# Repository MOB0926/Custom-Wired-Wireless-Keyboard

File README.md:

### Custom-Wired-Wireless-Keyboard

## What Is This?

- This is my entry for Hackclub's 'KEEB' YSWS

- I designed a Custom TKL keyboard. I designed a PCB and a 3D-Printed Case to house the PCB

- My keyboard features 80 Keys in the standard orientation and order of a keyboard. In addition to an EC11 Rotary encoder for Volume Adjustment and a 0.91 in OLED to display whatever I want. As the circuit is controlled by a WEMOS LOLIN ESP32 S3 Mini, I have included wireless functionality through its onboard BLE, along with an internal 18650 battery and charging unit to supply power during wireless use.

## Design Preview

## PCB

## Challenges 

- Price. PCBs over 100x100mm are very expensive, along with all the other components this may have been my most dificult project for finding cost effective solutions

- Size. The case is massive and no printer I own or have acces too will allow me to print this so I had to think about that as I designed.

- Procrastination. I had 3 months to do this and for some reason took like 3 week breaks in between entries at the begining

## What I learned

- This is my first time implementing a battery into a project so it was quite the new experience

- I have never designed or even built a Keyboard in my life (Excluding the Blueprint Hack-Pad) so I learnt a lot about how they work and the many different ways the case can come together.

- 3ple check every measurement before basing a design choice on it and then coming back after 4 hours of work just for it to be completetly wrong

## Why 

- Free Keyboard Obviously (Well if instead of putting all this time into this and I got a job instead I think I would have more than a $90 grant)

- Cool thing to show off

- Experience and knowledge for the future that will hopefully help me get a good career 

## CAD

- [OnShape Link](https://cad.onshape.com/documents/53f04297178249ea44cfb3cb/w/90fdca30b2683fca6e7d0462/e/9a4dc5cee2a441016592482a?renderMode=0&uiState=6ae65793278064ead9cd5df0)

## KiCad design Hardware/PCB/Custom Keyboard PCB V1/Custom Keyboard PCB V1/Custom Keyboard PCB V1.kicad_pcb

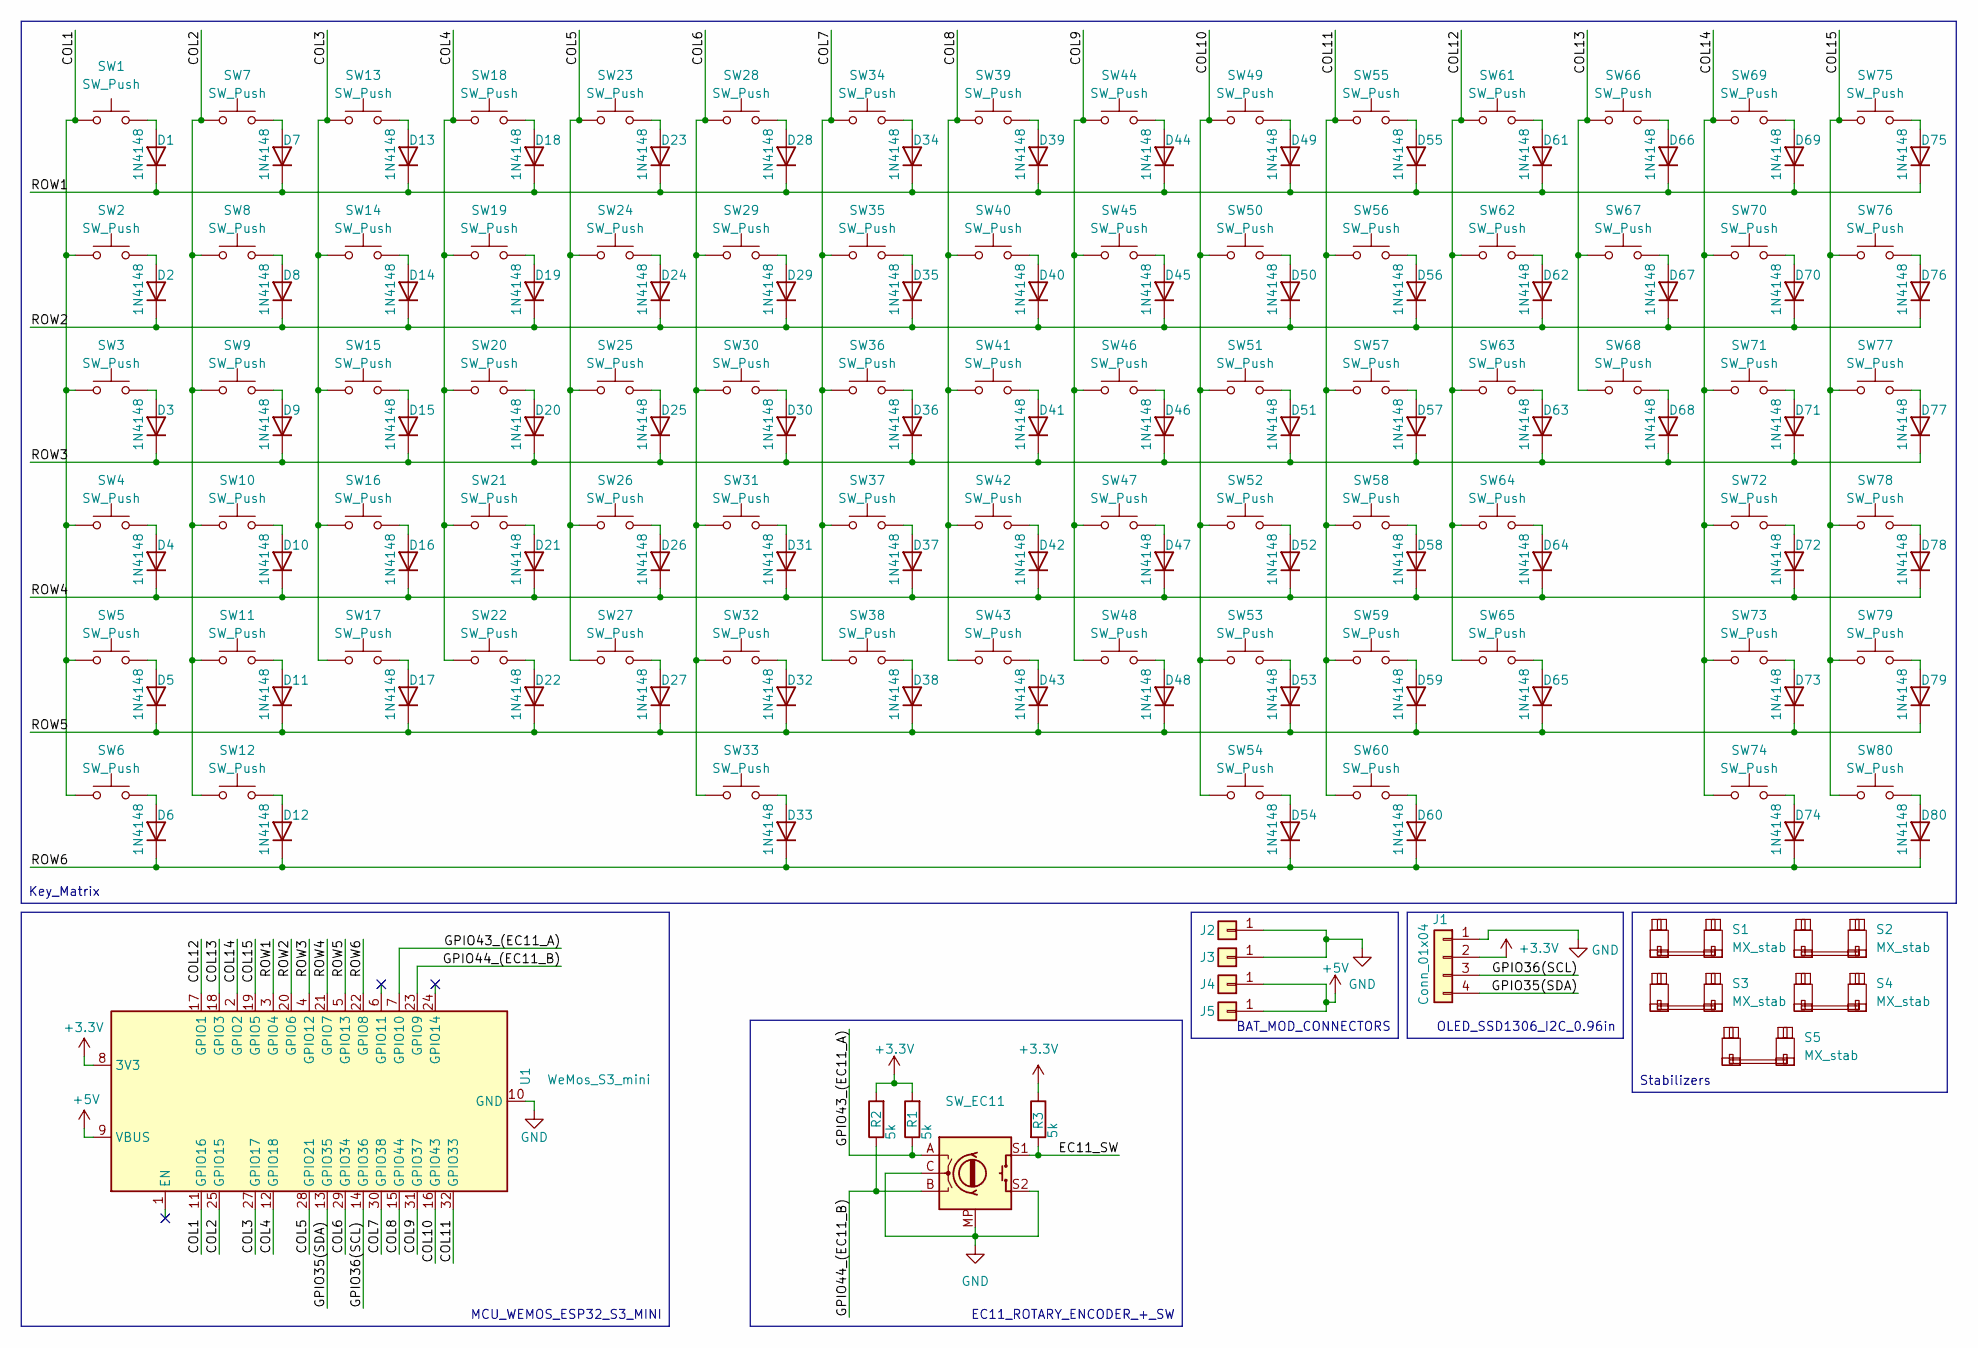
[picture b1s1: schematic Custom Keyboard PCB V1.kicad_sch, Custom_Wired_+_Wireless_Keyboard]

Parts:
D1, D2, D3, D4, D5, D6, D7, D8, D9, D10, D11, D12, D13, D14, D15, D16, D17, D18, D19, D20, D21, D22, D23, D24, D25, D26, D27, D28, D29, D30, D31, D32, D33, D34, D35, D36, D37, D38, D39, D40, D41, D42, D43, D44, D45, D46, D47, D48, D49, D50, D51, D52, D53, D54, D55, D56, D57, D58, D59, D60, D61, D62, D63, D64, D65, D66, D67, D68, D69, D70, D71, D72, D73, D74, D75, D76, D77, D78, D79, D80: 1N4148; D_MiniMELF_Handsoldering
J1: Conn_01x04; OLED_SSD1306_I2C_0.96
J2, J3, J4, J5: Conn_01x01; PinHeader_1x01_P2.54mm_Vertical
R1, R2, R3: 5k; R_Axial_DIN0204_L3.6mm_D1.6mm_P5.08mm_Horizontal
S1, S2, S3, S4: MX_stab; STAB_MX_P_2u
S5: MX_stab; STAB_MX_P_6.25u
SW1, SW2, SW3, SW4, SW5, SW6, SW7, SW8, SW9, SW10, SW11, SW12, SW13, SW14, SW15, SW16, SW17, SW18, SW19, SW20, SW21, SW22, SW23, SW24, SW25, SW26, SW27, SW28, SW29, SW30, SW31, SW32, SW33, SW34, SW35, SW36, SW37, SW38, SW39, SW40, SW41, SW42, SW43, SW44, SW45, SW46, SW47, SW48, SW49, SW50, SW51, SW52, SW53, SW54, SW55, SW56, SW57, SW58, SW59, SW60, SW61, SW62, SW63, SW64, SW65, SW66, SW67, SW68, SW69, SW70, SW71, SW72, SW73, SW74, SW75, SW76, SW77, SW78, SW79, SW80: SW_Push; SW_MX_1u
SW_EC11: RotaryEncoder_Switch_MP; RotaryEncoder_Alps_EC11E-Switch_Vertical_H20mm_MountingHoles
U1: WeMos_S3_mini; WEMOS_S2_mini

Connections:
+3.3V: J1.2, R1.2, R2.2, R3.1, U1.8 (3V3)
+5V: J4.1 (Pin_1_1), J5.1 (Pin_1_1), U1.9 (VBUS)
/COL1: SW1.1, SW2.1, SW3.1, SW4.1, SW5.1, SW6.1, U1.11 (GPIO16)
/COL2: SW7.1, SW8.1, SW9.1, SW10.1, SW11.1, SW12.1, U1.25 (GPIO15)
/COL3: SW13.1, SW14.1, SW15.1, SW16.1, SW17.1, U1.27 (GPIO17)
/COL4: SW18.1, SW19.1, SW20.1, SW21.1, SW22.1, U1.12 (GPIO18)
/COL5: SW23.1, SW24.1, SW25.1, SW26.1, SW27.1, U1.28 (GPIO21)
/COL6: SW28.1, SW29.1, SW30.1, SW31.1, SW32.1, SW33.1, U1.29 (GPIO34)
/COL7: SW34.1, SW35.1, SW36.1, SW37.1, SW38.1, U1.30 (GPIO38)
/COL8: SW39.1, SW40.1, SW41.1, SW42.1, SW43.1, U1.15 (GPIO44)
/COL9: SW44.1, SW45.1, SW46.1, SW47.1, SW48.1, U1.31 (GPIO37)
/COL10: SW49.1, SW50.1, SW51.1, SW52.1, SW53.1, SW54.1, U1.16 (GPIO43)
/COL11: SW55.1, SW56.1, SW57.1, SW58.1, SW59.1, SW60.1, U1.32 (GPIO33)
/COL12: SW61.1, SW62.1, SW63.1, SW64.1, SW65.1, U1.17 (GPIO1)
/COL13: SW66.1, SW67.1, SW68.1, U1.18 (GPIO3)
/COL14: SW69.1, SW70.1, SW71.1, SW72.1, SW73.1, SW74.1, U1.2 (GPIO2)
/COL15: SW75.1, SW76.1, SW77.1, SW78.1, SW79.1, SW80.1, U1.19 (GPIO5)
/EC11_SW: R3.2, SW_EC11.S1
/GPIO35(SDA): J1.4, U1.13 (GPIO35)
/GPIO36(SCL): J1.3, U1.14 (GPIO36)
/GPIO43_(EC11_A): R1.1, SW_EC11.A, U1.7 (GPIO10)
/GPIO44_(EC11_B): R2.1, SW_EC11.B, U1.23 (GPIO9)
/ROW1: D1.1 (K), D7.1 (K), D13.1 (K), D18.1 (K), D23.1 (K), D28.1 (K), D34.1 (K), D39.1 (K), D44.1 (K), D49.1 (K), D55.1 (K), D61.1 (K), D66.1 (K), D69.1 (K), D75.1 (K), U1.3 (GPIO4)
/ROW2: D2.1 (K), D8.1 (K), D14.1 (K), D19.1 (K), D24.1 (K), D29.1 (K), D35.1 (K), D40.1 (K), D45.1 (K), D50.1 (K), D56.1 (K), D62.1 (K), D67.1 (K), D70.1 (K), D76.1 (K), U1.20 (GPIO6)
/ROW3: D3.1 (K), D9.1 (K), D15.1 (K), D20.1 (K), D25.1 (K), D30.1 (K), D36.1 (K), D41.1 (K), D46.1 (K), D51.1 (K), D57.1 (K), D63.1 (K), D68.1 (K), D71.1 (K), D77.1 (K), U1.4 (GPIO12)
/ROW4: D4.1 (K), D10.1 (K), D16.1 (K), D21.1 (K), D26.1 (K), D31.1 (K), D37.1 (K), D42.1 (K), D47.1 (K), D52.1 (K), D58.1 (K), D64.1 (K), D72.1 (K), D78.1 (K), U1.21 (GPIO7)
/ROW5: D5.1 (K), D11.1 (K), D17.1 (K), D22.1 (K), D27.1 (K), D32.1 (K), D38.1 (K), D43.1 (K), D48.1 (K), D53.1 (K), D59.1 (K), D65.1 (K), D73.1 (K), D79.1 (K), U1.5 (GPIO13)
/ROW6: D6.1 (K), D12.1 (K), D33.1 (K), D54.1 (K), D60.1 (K), D74.1 (K), D80.1 (K), U1.22 (GPIO8)
GND: J1.1, J2.1 (Pin_1_1), J3.1 (Pin_1_1), SW_EC11.C, SW_EC11.MP, SW_EC11.S2, U1.10 (GND), U1.26 (GND)
unnamed: D1.2 (A), SW1.2
unnamed: D2.2 (A), SW2.2
unnamed: D3.2 (A), SW3.2
unnamed: D4.2 (A), SW4.2
unnamed: D5.2 (A), SW5.2
unnamed: D6.2 (A), SW6.2
unnamed: D7.2 (A), SW7.2
unnamed: D8.2 (A), SW8.2
unnamed: D9.2 (A), SW9.2
unnamed: D10.2 (A), SW10.2
unnamed: D11.2 (A), SW11.2
unnamed: D12.2 (A), SW12.2
unnamed: D13.2 (A), SW13.2
unnamed: D14.2 (A), SW14.2
unnamed: D15.2 (A), SW15.2
unnamed: D16.2 (A), SW16.2
unnamed: D17.2 (A), SW17.2
unnamed: D18.2 (A), SW18.2
unnamed: D19.2 (A), SW19.2
unnamed: D20.2 (A), SW20.2
unnamed: D21.2 (A), SW21.2
unnamed: D22.2 (A), SW22.2
unnamed: D23.2 (A), SW23.2
unnamed: D24.2 (A), SW24.2
unnamed: D25.2 (A), SW25.2
unnamed: D26.2 (A), SW26.2
unnamed: D27.2 (A), SW27.2
unnamed: D28.2 (A), SW28.2
unnamed: D29.2 (A), SW29.2
unnamed: D30.2 (A), SW30.2
unnamed: D31.2 (A), SW31.2
unnamed: D32.2 (A), SW32.2
unnamed: D33.2 (A), SW33.2
unnamed: D34.2 (A), SW34.2
unnamed: D35.2 (A), SW35.2
unnamed: D36.2 (A), SW36.2
unnamed: D37.2 (A), SW37.2
unnamed: D38.2 (A), SW38.2
unnamed: D39.2 (A), SW39.2
unnamed: D40.2 (A), SW40.2
unnamed: D41.2 (A), SW41.2
unnamed: D42.2 (A), SW42.2
unnamed: D43.2 (A), SW43.2
unnamed: D44.2 (A), SW44.2
unnamed: D45.2 (A), SW45.2
unnamed: D46.2 (A), SW46.2
unnamed: D47.2 (A), SW47.2
unnamed: D48.2 (A), SW48.2
unnamed: D49.2 (A), SW49.2
unnamed: D50.2 (A), SW50.2
unnamed: D51.2 (A), SW51.2
unnamed: D52.2 (A), SW52.2
unnamed: D53.2 (A), SW53.2
unnamed: D54.2 (A), SW54.2
unnamed: D55.2 (A), SW55.2
unnamed: D56.2 (A), SW56.2
unnamed: D57.2 (A), SW57.2
unnamed: D58.2 (A), SW58.2
unnamed: D59.2 (A), SW59.2
unnamed: D60.2 (A), SW60.2
unnamed: D61.2 (A), SW61.2
unnamed: D62.2 (A), SW62.2
unnamed: D63.2 (A), SW63.2
unnamed: D64.2 (A), SW64.2
unnamed: D65.2 (A), SW65.2
unnamed: D66.2 (A), SW66.2
unnamed: D67.2 (A), SW67.2
unnamed: D68.2 (A), SW68.2
unnamed: D69.2 (A), SW69.2
unnamed: D70.2 (A), SW70.2
unnamed: D71.2 (A), SW71.2
unnamed: D72.2 (A), SW72.2
unnamed: D73.2 (A), SW73.2
unnamed: D74.2 (A), SW74.2
unnamed: D75.2 (A), SW75.2
unnamed: D76.2 (A), SW76.2
unnamed: D77.2 (A), SW77.2
unnamed: D78.2 (A), SW78.2
unnamed: D79.2 (A), SW79.2
unnamed: D80.2 (A), SW80.2

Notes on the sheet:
OLED_SSD1306_I2C_0.96in
BAT_MOD_CONNECTORS
MCU_WEMOS_ESP32_S3_MINI
Key_Matrix
EC11_ROTARY_ENCODER_+_SW
Stabilizers

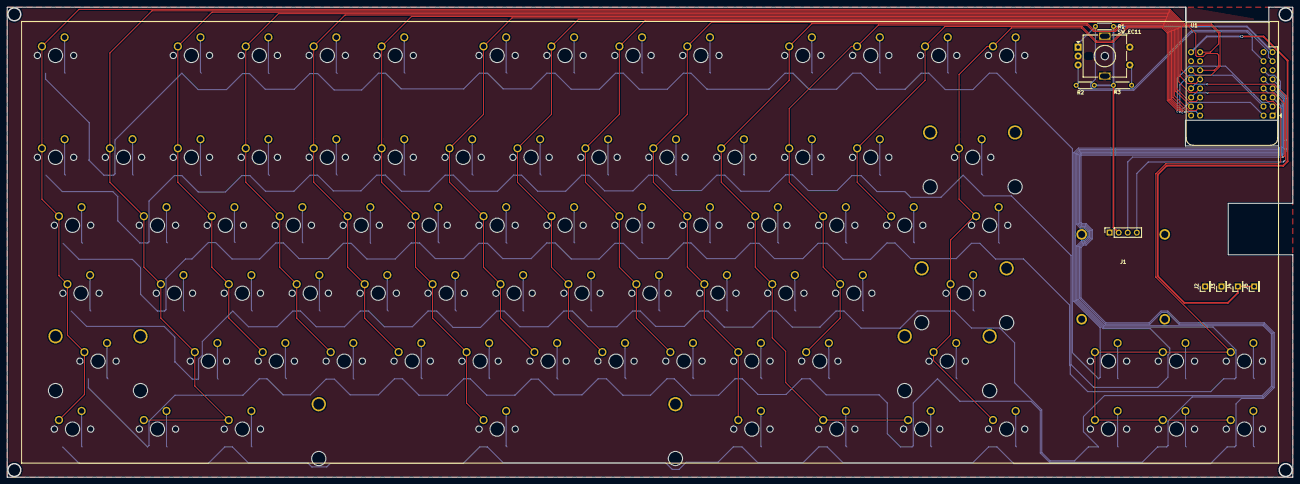
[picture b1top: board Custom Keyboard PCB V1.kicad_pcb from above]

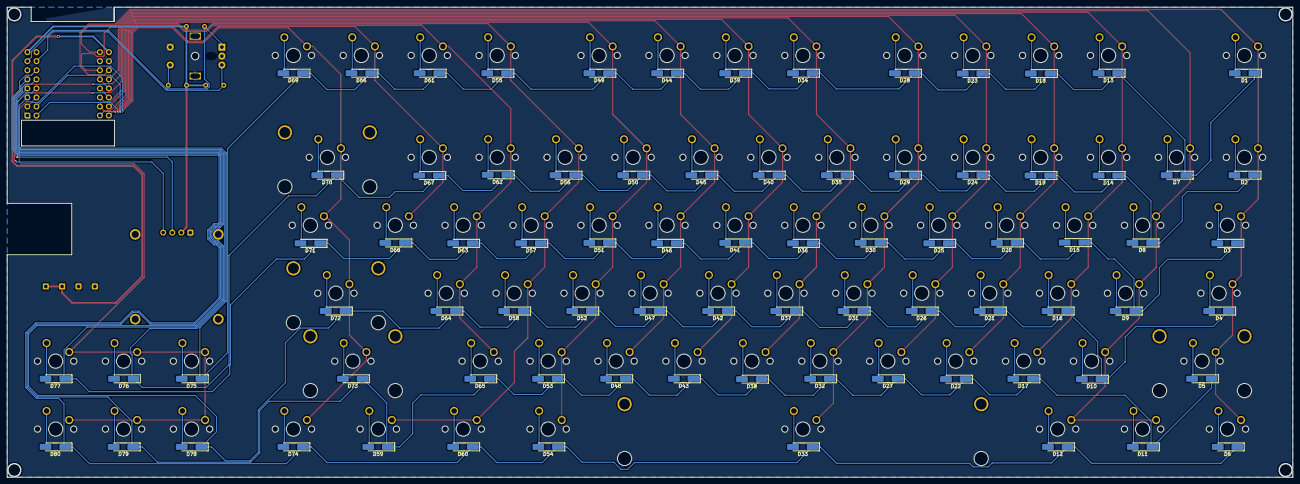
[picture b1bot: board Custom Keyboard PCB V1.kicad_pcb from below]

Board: 2 copper layers, 360.5 x 131.8 mm, 175 parts (80 on the bottom side), 109 nets.

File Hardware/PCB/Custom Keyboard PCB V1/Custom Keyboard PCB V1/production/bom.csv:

Designator,Footprint,Quantity,Value,LCSC Part #
"D1, D10, D11, D12, D13, D14, D15, D16, D17, D18, D19, D2, D20, D21, D22, D23, D24, D25, D26, D27, D28, D29, D3, D30, D31, D32, D33, D34, D35, D36, D37, D38, D39, D4, D40, D41, D42, D43, D44, D45, D46, D47, D48, D49, D5, D50, D51, D52, D53, D54, D55, D56, D57, D58, D59, D6, D60, D61, D62, D63, D64, D65, D66, D67, D68, D69, D7, D70, D71, D72, D73, D74, D75, D76, D77, D78, D79, D8, D80, D9",D_MiniMELF_Handsoldering,80,1N4148,
J1,OLED_SSD1306_I2C_0.96,1,Conn_01x04,
"J2, J3, J4, J5",PinHeader_1x01_P2.54mm_Vertical,4,Conn_01x01,
"R1, R2, R3",R_Axial_DIN0204_L3.6mm_D1.6mm_P5.08mm_Horizontal,3,5k,
"S1, S2, S3, S4",STAB_MX_P_2u,4,MX_stab,
S5,STAB_MX_P_6.25u,1,MX_stab,
"SW1, SW10, SW11, SW12, SW13, SW14, SW15, SW16, SW17, SW18, SW19, SW2, SW20, SW21, SW22, SW23, SW24, SW25, SW26, SW27, SW28, SW29, SW3, SW30, SW31, SW32, SW33, SW34, SW35, SW36, SW37, SW38, SW39, SW4, SW40, SW41, SW42, SW43, SW44, SW45, SW46, SW47, SW48, SW49, SW5, SW50, SW51, SW52, SW53, SW54, SW55, SW56, SW57, SW58, SW59, SW6, SW60, SW61, SW62, SW63, SW64, SW65, SW66, SW67, SW68, SW69, SW7, SW70, SW71, SW72, SW73, SW74, SW75, SW76, SW77, SW78, SW79, SW8, SW80, SW9",SW_MX_1u,80,SW_Push,
SW_EC11,RotaryEncoder_Alps_EC11E-Switch_Vertical_H20mm_MountingHoles,1,RotaryEncoder_Switch_MP,
U1,WEMOS_S2_mini,1,WeMos_S3_mini,
